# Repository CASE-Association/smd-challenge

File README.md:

(Currently work in progress)

# CASE SMD Challenge

Inspired by [this unfortunate SMD project](https://hackaday.io/project/25265-an-unfortunate-smd-project) we have created the CASE SMD Challenge to provide our members with an opportunity for immense soldering frustration. If you are able to fully assemble the board it also doubles as  a small USB development board. You can now flash all the LED:s that were painstakingly added to the board or hook it up to other gizmos via the test points on the PCB.

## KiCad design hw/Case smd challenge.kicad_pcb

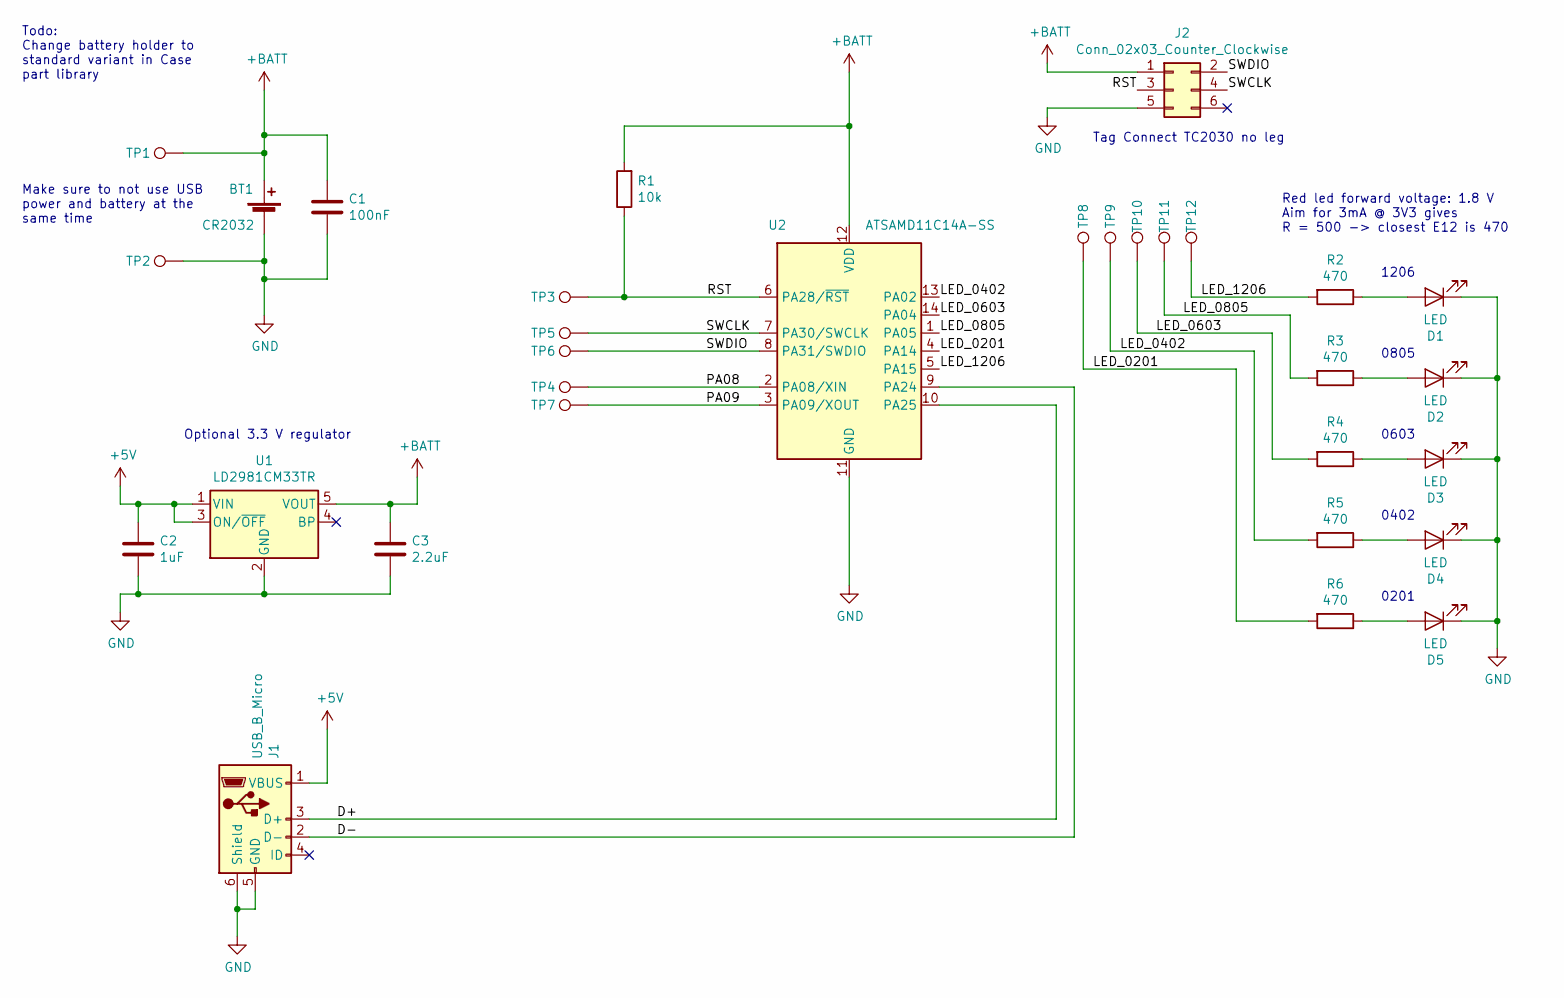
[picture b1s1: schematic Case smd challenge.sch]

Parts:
BT1: CR2032; BatteryHolder_Keystone_3002_1x2032; MPN 3002TR
C1: 100nF; C_0603_1608Metric
C2: 1uF; C_0603_1608Metric
C3: 2.2uF; C_0603_1608Metric
D1: LED; LED_1206_3216Metric; MPN 150120RS75000
D2: LED; LED_0805_2012Metric; MPN LH R974-LP-1
D3: LED; LED_0603_1608Metric; MPN SML-D12U1WT86
D4: LED; LED_0402_1005Metric; MPN SML-P12VTT86R
D5: LED; LED_0201_0603Metric; MPN APG0603SEC-E-TT
J1: USB_B_Micro; USB_Micro-B_Molex-105017-0001
J2: Conn_02x03_Counter_Clockwise; Tag-Connect_TC2030-IDC-NL_2x03_P1.27mm_Vertical
R1: 10k; R_0603_1608Metric
R2: 470; R_1206_3216Metric; MPN RMCF1206JT470R
R3: 470; R_0805_2012Metric; MPN RMCF0805JT470R
R4: 470; R_0603_1608Metric; MPN RMCF0603JT470R
R5: 470; R_0402_1005Metric; MPN RMCF0402JT470R
R6: 470; R_0201_0603Metric; MPN RMCF0201JT470R
TP1, TP2, TP3, TP4, TP5, TP6, TP7, TP8, TP9, TP10, TP11, TP12: TestPoint; TestPoint_Pad_D1.0mm
U1: LD2981CM33TR; SOT-23-5
U2: ATSAMD11C14A-SS; SOIC-14_3.9x8.7mm_P1.27mm; MPN ATSAMD11C14A-SSUT

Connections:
+5V: C2.1, J1.1 (VBUS), U1.1 (VIN), U1.3 (ON/~OFF~)
+BATT: BT1.1 (+), C1.1, C3.1, J2.1, R1.2, TP1.1, U1.5 (VOUT), U2.12 (VDD)
/D+: J1.3 (D+), U2.10 (PA25)
/D-: J1.2 (D-), U2.9 (PA24)
/LED_0201: R6.2, TP8.1, U2.4 (PA14)
/LED_0402: R5.2, TP9.1, U2.13 (PA02)
/LED_0603: R4.2, TP10.1, U2.14 (PA04)
/LED_0805: R3.2, TP11.1, U2.1 (PA05)
/LED_1206: R2.2, TP12.1, U2.5 (PA15)
/PA08: TP4.1, U2.2 (PA08/XIN)
/PA09: TP7.1, U2.3 (PA09/XOUT)
/RST: J2.3, R1.1, TP3.1, U2.6 (PA28/~RST)
/SWCLK: J2.4, TP5.1, U2.7 (PA30/SWCLK)
/SWDIO: J2.2, TP6.1, U2.8 (PA31/SWDIO)
GND: BT1.2 (-), C1.2, C2.2, C3.2, D1.1 (K), D2.1 (K), D3.1 (K), D4.1 (K), D5.1 (K), J1.5 (GND), J1.6 (Shield), J2.5, TP2.1, U1.2 (GND), U2.11 (GND)
unnamed: D1.2 (A), R2.1
unnamed: D2.2 (A), R3.1
unnamed: D3.2 (A), R4.1
unnamed: D4.2 (A), R5.1
unnamed: D5.2 (A), R6.1

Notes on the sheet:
0805
0603
0402
0201
1206
Optional 3.3 V regulator
Make sure to not use USB power and battery at the same time
Tag Connect TC2030 no leg
Red led forward voltage: 1.8 V Aim for 3mA @ 3V3 gives R = 500 -> closest E12 is 470
Todo: Change battery holder to standard variant in Case part library

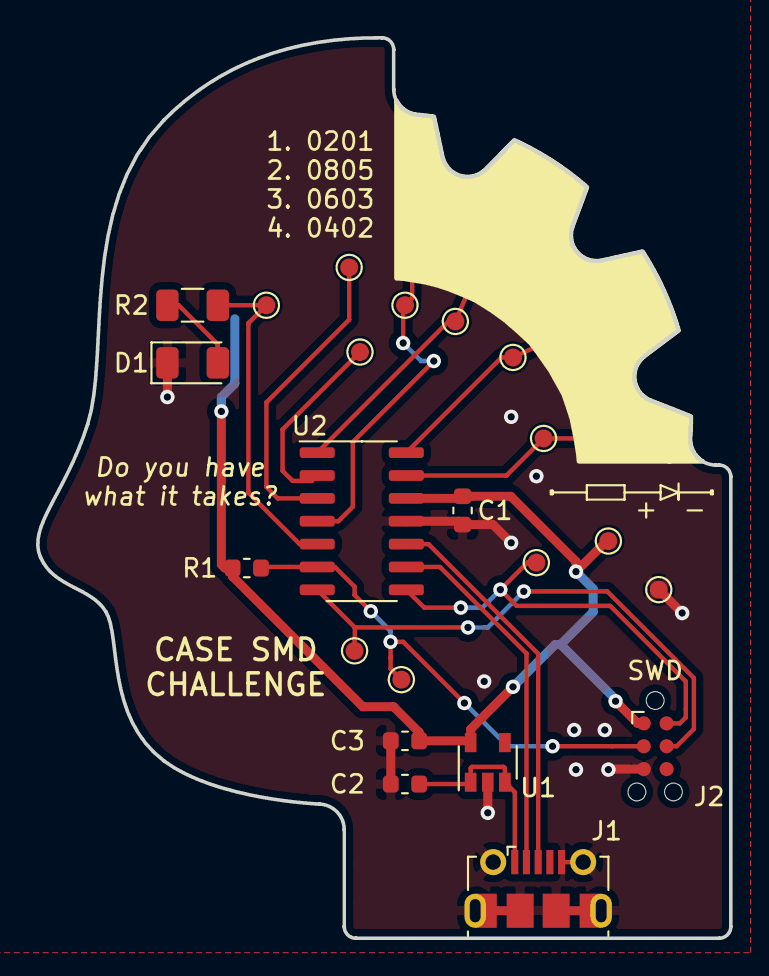
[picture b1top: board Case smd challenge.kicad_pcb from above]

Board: 2 copper layers, 38.5 x 50.0 mm, 31 parts (1 on the bottom side), 20 nets.

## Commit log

2021-03-17 Initial commit of first revision
